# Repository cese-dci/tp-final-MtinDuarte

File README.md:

## Trabajo práctico final de la asignatura DCI ##
Este repositorio contiene el trabajo práctico final para la asignatura de Diseño de Circuitos Impresos de la carrera de posgrado de FIUBA.

* Autor: Martin Duarte
* Título corto del trabajo:  Replica módulo driver PWM con SG3525 ajustable
* Descripción: La placa comercial corresponde a la sección de drivers PWM y puede ser utilizado en gran variedad de aplicaciones desde fuentes de alimentación de tipo switching, convertidores DC-DC, control de velocidad de motores, dimmer de LED, fuentes de alimentación de alto voltaje, drivers de solenoide o carga electrónica. Es un chip de bajo costo el cual  posee ajuste en frecuencia, duty, y arranque suave (opcional). Es posible obtener pulsos de lógica TTL o 12V gracias a la selección del modo de funcionamiento con uno de los Jumpers de la placa. La integrado es capaz de funcionar como driver de MOSFET directamente. 

## Licencia de este trabajo ##
Este trabajo se encontrará enmarcado bajo licencia "Creative Commons Attribution-ShareAlike"

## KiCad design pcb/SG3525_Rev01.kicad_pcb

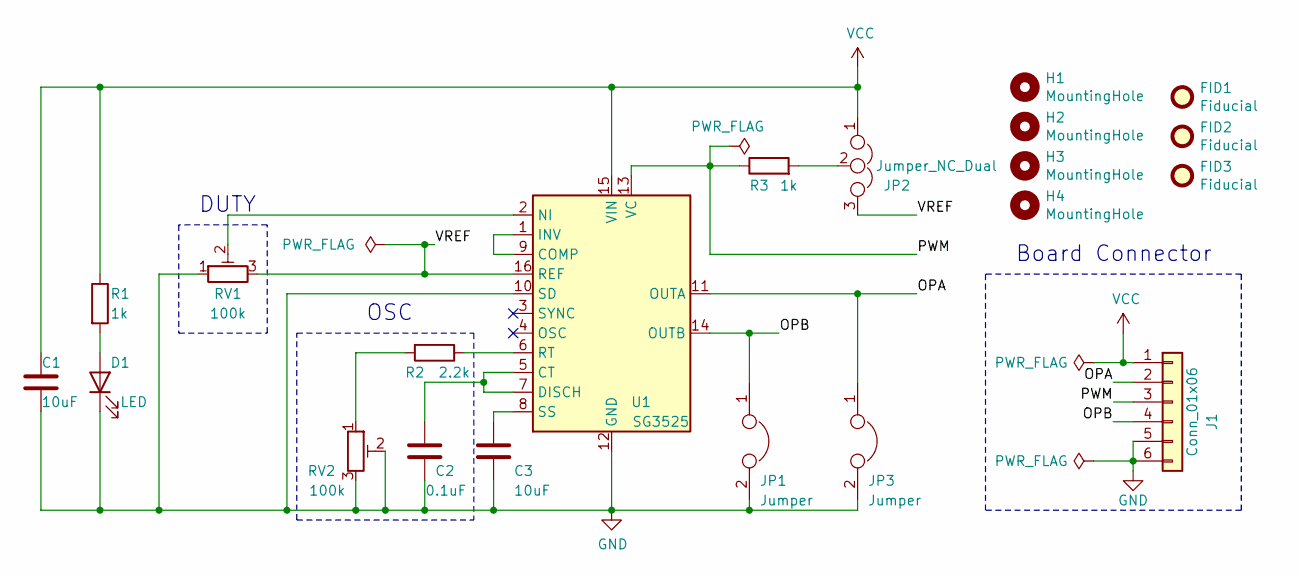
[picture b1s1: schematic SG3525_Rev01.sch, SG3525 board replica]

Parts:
C1: 10uF; CP_EIA-1608-10_AVX-L; Manufacture Part T95V155K035HSSL
C2: 0.1uF; CP_EIA-1608-10_AVX-L
C3: 10uF; CP_EIA-1608-10_AVX-L
D1: LED; LED_0805_2012Metric; DigikeyPart 3372-0805RBD0070S01TR-ND
FID1, FID2, FID3: Fiducial; Fiducial_1mm_Mask2mm
H1, H2, H3, H4: MountingHole; MountingHole_2.2mm_M2_DIN965_Pad
J1: Conn_01x06; PinHeader_1x06_P2.54mm_Vertical
JP1, JP3: Jumper; PinHeader_1x02_P2.54mm_Vertical
JP2: Jumper_NC_Dual; PinHeader_1x03_P2.54mm_Vertical
R1, R3: 1k; R_0805_2012Metric
R2: 2.2k; R_0805_2012Metric
RV1, RV2: 100k; Potentiometer_Piher_PT-6-V_Vertical
U1: SG3525; SOP-16_4.4x10.4mm_P1.27mm; Manufacture Part SG3525AP013TR

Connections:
/OPA: J1.2, JP3.1, U1.11 (OUTA)
/OPB: J1.4, JP1.1, U1.14 (OUTB)
/PWM: J1.3, R3.1, U1.13 (VC)
/VREF: JP2.3, RV1.3, U1.16 (REF)
GND: C1.2, C2.2, C3.2, D1.1 (K), J1.5, J1.6, JP1.2, JP3.2, RV1.1, RV2.2, RV2.3, U1.10 (SD), U1.12 (GND)
unnamed: C2.1, U1.5 (CT), U1.7 (DISCH)
unnamed: C3.1, U1.8 (SS)
unnamed: D1.2 (A), R1.2
unnamed: JP2.2, R3.2
unnamed: R2.1, U1.6 (RT)
unnamed: R2.2, RV2.1
unnamed: RV1.2, U1.2 (NI)
unnamed: U1.1 (INV), U1.9 (COMP)
VCC: C1.1, J1.1, JP2.1, R1.1, U1.15 (VIN)

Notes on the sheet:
Board Connector
OSC
DUTY

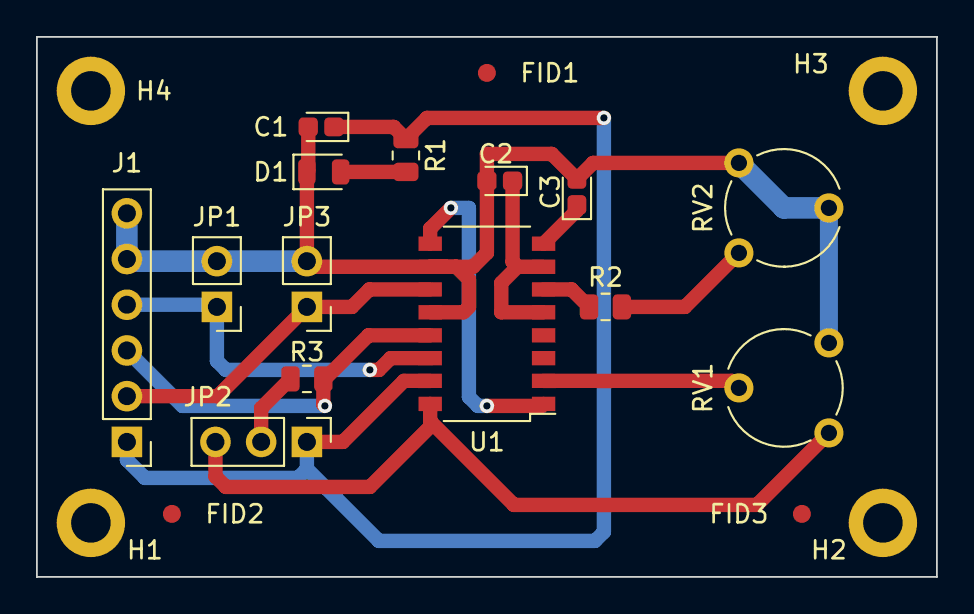
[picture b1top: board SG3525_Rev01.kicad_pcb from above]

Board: 2 copper layers, 50.0 x 30.0 mm, 21 parts (0 on the bottom side), 14 nets.

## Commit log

2021-09-21 Adding images folder, and datasheet
2021-09-21 Update Readme
    Agrego imágenes, falta completar aún.
2021-09-21 Update readme
    Agrego información de propuesta.
2021-09-22 Agrego archivos de kicad y datasheet de SG3525
2021-09-22 Subo archivos de kicad y datasheet de SG3525
2021-09-23 Correct global labels for locals
2021-09-25 Last changes after .sch presentation
2021-10-11 Agrego archivos con PCB ruteado
2021-10-11 Añado archivo step, y algunos cambios en la pc menores
2021-10-11 pcb update
2021-10-14 Añado archivos de fabricación, últimos detalles despues de la presentación

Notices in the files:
pcb/SG3525_Rev01.kicad_pcb:
Under Creative Commons (CC)  license
pcb/SG3525_Rev01.sch:
Under Creative Commons ( CC )  licence.
